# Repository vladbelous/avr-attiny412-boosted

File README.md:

# ATtiny412-based board with on-board boost regulator

Small ATtiny412 board powered by a boost regulator (MCP1640, or pin-compatible MCP16251, TPS6107x; check FB voltage).

Two powering options:
* Li-Ion battery: place voltage-supervisor MIC809 (U2) and R2 pull-down resistor -- this will protect the battery from discharging below 2.93V.
* Single/double AA battery: can skip MIC809 and place R1 instead -- this will put boost regulator in always-on mode.

Optional:
* Power distribution switch IC (MIC9409x) for the common use case of driving a LED strip (WS2812B, APA106, etc), or other, possibly capacitative, loads.
* Pull-up resistors for I2C on botton side (on pins PA1 = SDA, and PA2 = SCL).

Designed with KiCad 5 (www.kicad.org).

## Schematic:

## Layout:

## Assembled:

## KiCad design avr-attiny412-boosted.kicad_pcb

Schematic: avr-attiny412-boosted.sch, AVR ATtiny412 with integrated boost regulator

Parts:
C1: 10uF; 1206_HS
C2: 4.7uF; 1206_HS
C3, C5: 10uF; 1210_HS
C4: 0.1uF; 0805_HS
F1: Polyfuse; 1206_HS
J2, J3, J4, J5, J6, J7, J8, J9, J13, J14, J15: Conn_01x01; Pin_Header_Straight_1x01_Pitch2.54mm
J10, J11, J12: Conn_01x01; Conn_1-wire
JST_PH_BAT1: JST_PH_BAT; JST_PH_S2B-PH-K_02x2.00mm_Angled_WiderHole
L1: 4.7uH; L_Taiyo-Yuden_NR-S-40xx_HS
R1, R2, R6: 100k; 0805_HS
R3, R4: R; 0805_HS
R5: 3.3k; 0805_HS
R7: 1k; 0805_HS
R8, R9: 10k; 0805_HS
SW1: SW_Push; SW_SPST_PUSH_6mm_3mm
U1: MCP1640; SOT-23-6_HS
U2: MIC809; SOT-23_HS
U3: attiny412; SOIC-8_3.9x4.9mm_Pitch1.27mm_HS
U4: MIC9409x; SOT-363_SC-70-6_HS

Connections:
GND: C1.2, C2.2, C3.2, C4.2, C5.2, J5.1, J9.1, J12.1, J15.1, JST_PH_BAT1.2, R2.2, R4.2, R6.2, SW1.2, U1.2, U2.1, U3.8, U4.2, U4.5
unnamed: F1.2, JST_PH_BAT1.1
unnamed: J14.1, R7.1
unnamed: L1.2, U1.1
unnamed: R1.2, R2.1, U1.3, U2.2
unnamed: R3.2, R4.1, U1.4
unnamed: R5.2, SW1.1, U3.6
PA1: J2.1, R8.2, U3.4
PA2: J3.1, R9.2, U3.5
PA3: J4.1, U3.7
PA6: J7.1, R6.1, U3.2, U4.6
PA7: J8.1, R7.2, U3.3
UPDI: J11.1, R5.1
VBAT: C1.1, F1.1, L1.1, R1.1, U1.6, U2.3
VPP: C2.1, C3.1, C4.1, J6.1, J10.1, R3.1, R8.1, R9.1, U1.5, U3.1, U4.4
VSW: C5.1, J13.1, U4.1

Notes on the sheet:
Place either: R2 + MIC809: voltage supervisor enabled (useful when using Li-Ion batteries) or R1: bypass superviser, boost always on (useful when using non-rechargeable)
DNP
Vth = 2.93V
750mA
Pin-compatible with: MCP1640: FB = 1.21V MCP16251: FB = 1.23V TPS61070 / TPS61073: FB = 0.5V
SW1: reset in software or other functionality
optional I2C pull-ups
3 smaller PTHs for programming
Load switch, controlled with PA6
LED strip with data on PA7
push-pull

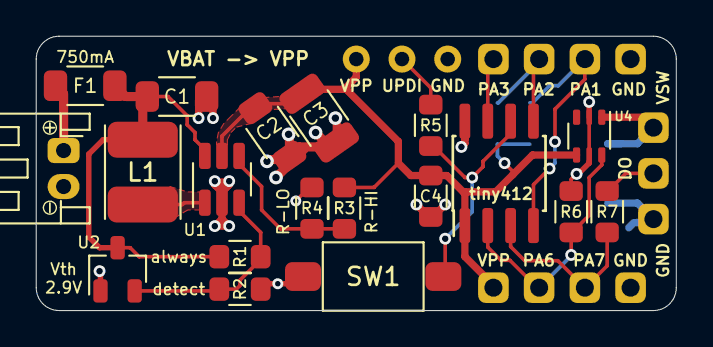
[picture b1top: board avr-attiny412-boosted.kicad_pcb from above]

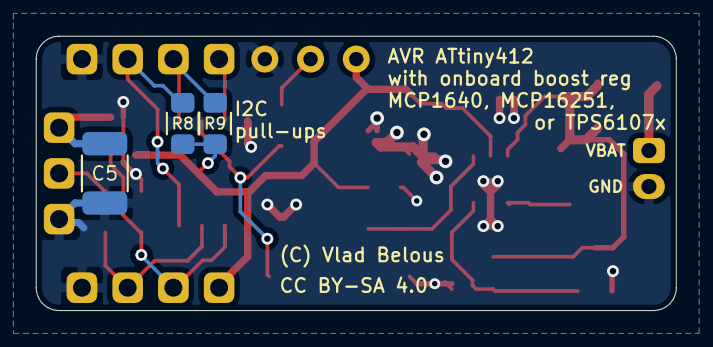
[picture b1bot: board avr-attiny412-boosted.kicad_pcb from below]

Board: 2 copper layers, 35.6 x 15.2 mm, 36 parts (3 on the bottom side), 16 nets.

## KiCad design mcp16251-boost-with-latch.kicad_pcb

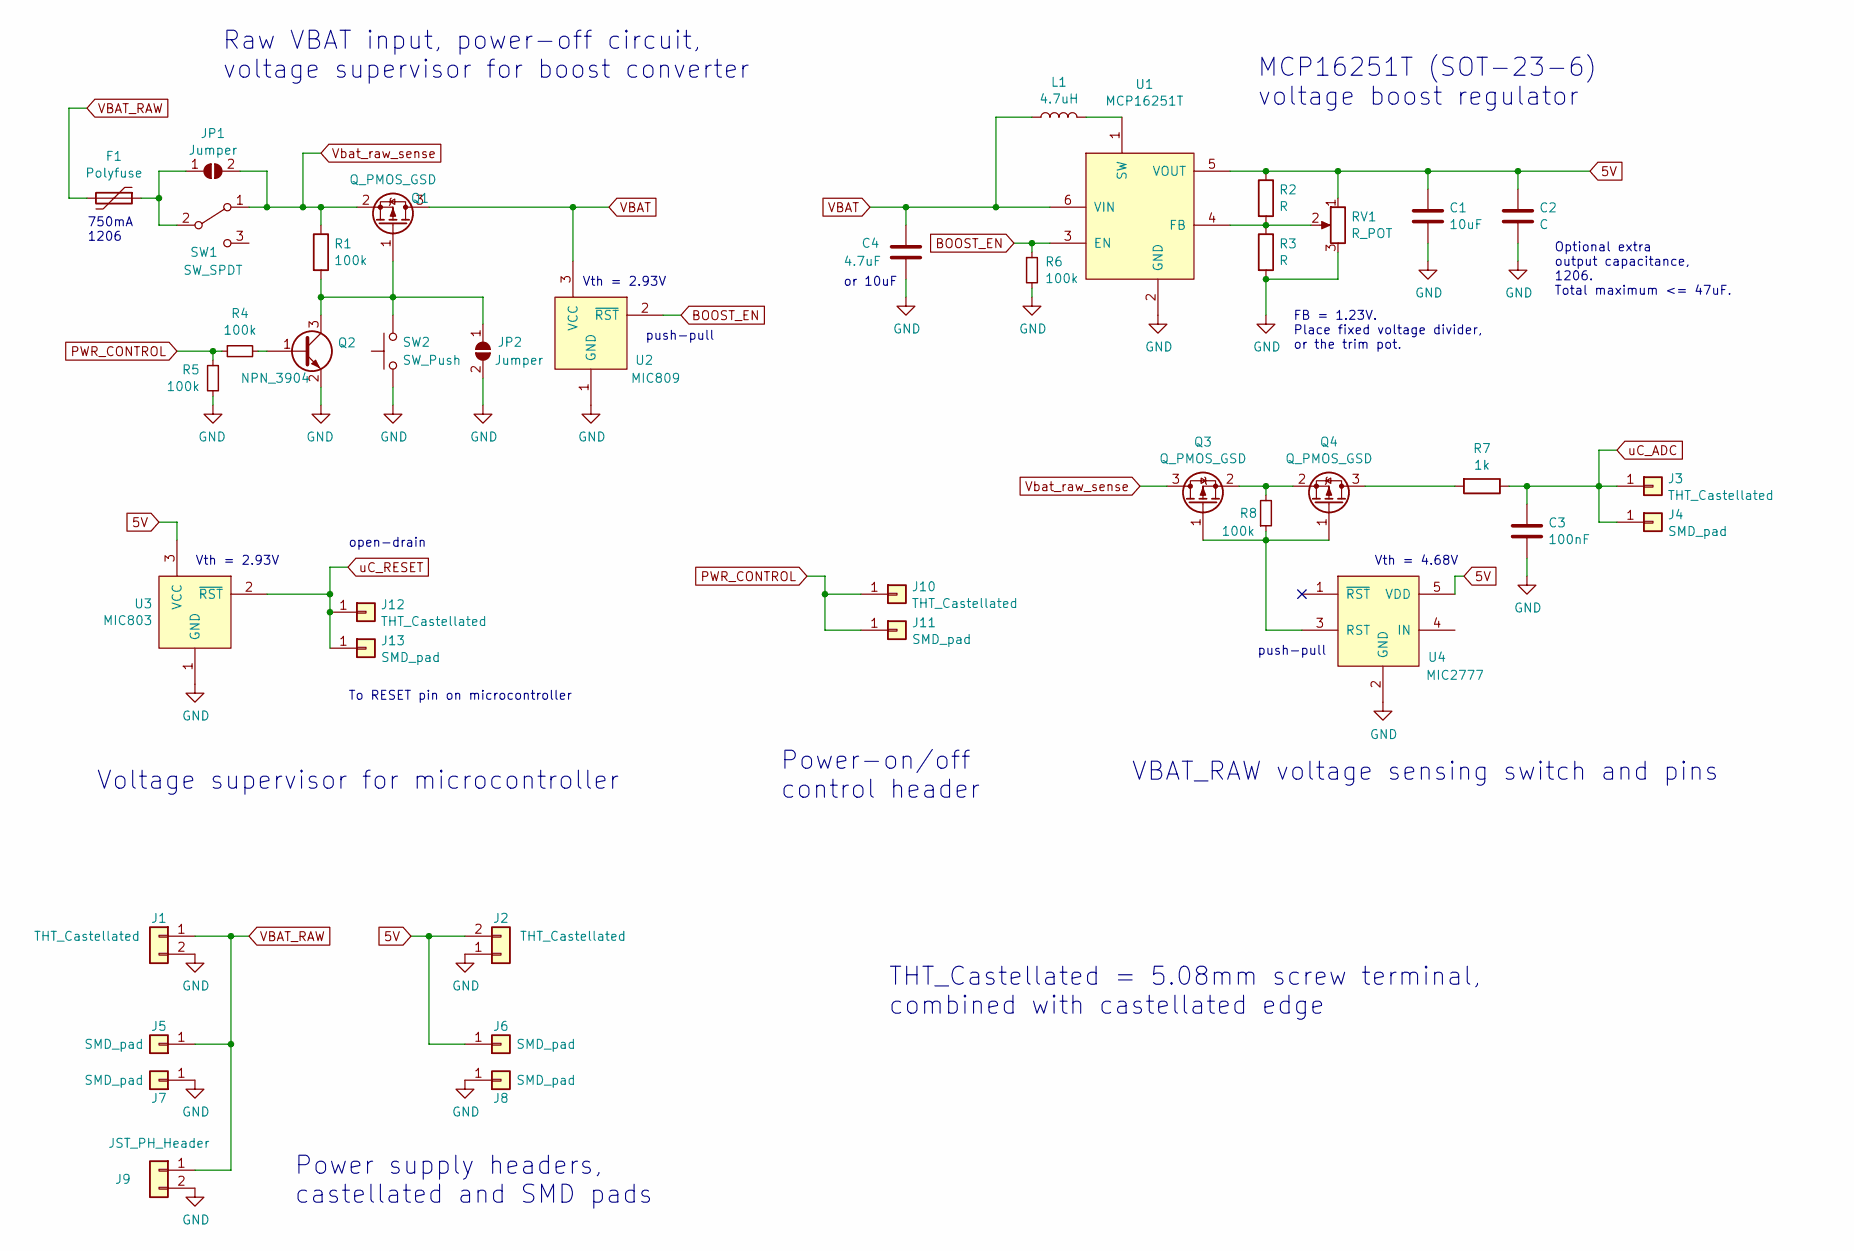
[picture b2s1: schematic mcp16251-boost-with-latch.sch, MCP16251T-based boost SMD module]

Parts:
C1: 10uF; R_1206_HS
C2: C; R_1206_HS
C3: 100nF; R_0805_HS
C4: 4.7uF; R_1206_HS
F1: Polyfuse; R_1206_HS
J1: THT_Castellated; Conn_01x02_cast
J2: THT_Castellated; Conn_01x02_cast_mirrored
J3, J10, J12: THT_Castellated; Conn_01x01_cast
J4, J5, J6, J7, J8, J11, J13: SMD_pad; SMD-Pad_01x01
J9: JST_PH_Header; JST_PH_S2B-PH-K_02x2.00mm_Angled
JP1, JP2: Jumper; R_0805_HS
L1: 4.7uH; L_Taiyo-Yuden_NR-S-40xx_HS
Q1, Q3, Q4: Q_PMOS_GSD; SOT-23_HS
Q2: NPN_3904; SOT-23_HS
R1, R4, R5, R6, R8: 100k; R_0805_HS
R2, R3: R; R_0805_HS
R7: 1k; R_0805_HS
RV1: R_POT; Conn_01x03_small
SW1: SW_SPDT; Conn_01x03_small
SW2: SW_Push; SW_SPST_TL3342
U1: MCP16251T; SOT-23-6_HS
U2: MIC809; SOT-23_HS
U3: MIC803; SOT-23_HS
U4: MIC2777; SOT-23-5_HS

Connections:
5V: C1.1, C2.1, J2.2, J6.1, R2.1, RV1.1, U1.5 (VOUT), U3.3 (VCC), U4.5 (VDD)
BOOST_EN: R6.1, U1.3 (EN), U2.2 (~RST)
GND: C1.2, C2.2, C3.2, C4.2, J1.2, J2.1, J7.1, J8.1, J9.2, JP2.2 (B), Q2.2 (E), R3.2, R5.2, R6.2, RV1.3, SW2.1, U1.2 (GND), U2.1 (GND), U3.1 (GND), U4.2 (GND)
unnamed: F1.1, JP1.1 (A), SW1.2 (B)
unnamed: JP2.1 (A), Q1.1 (G), Q2.3 (C), R1.2, SW2.2
unnamed: L1.2, U1.1 (SW)
unnamed: Q2.1 (B), R4.2
unnamed: Q3.1 (G), Q4.1 (G), R8.1, U4.3 (RST)
unnamed: Q3.2 (S), Q4.2 (S), R8.2
unnamed: Q4.3 (D), R7.2
unnamed: R2.2, R3.1, RV1.2, U1.4 (FB)
PWR_CONTROL: J10.1, J11.1, R4.1, R5.1
VBAT: C4.1, L1.1, Q1.3 (D), U1.6 (VIN), U2.3 (VCC)
VBAT_RAW: F1.2, J1.1, J5.1, J9.1
Vbat_raw_sense: JP1.2 (B), Q1.2 (S), Q3.3 (D), R1.1, SW1.1 (A)
uC_ADC: C3.1, J3.1, J4.1, R7.1
uC_RESET: J12.1, J13.1, U3.2 (~RST)

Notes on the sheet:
Raw VBAT input, power-off circuit, voltage supervisor for boost converter
FB = 1.23V. Place fixed voltage divider, or the trim pot.
MCP16251T (SOT-23-6) voltage boost regulator
or 10uF
Optional extra output capacitance, 1206. Total maximum <= 47uF.
THT_Castellated = 5.08mm screw terminal, combined with castellated edge
Vth = 2.93V
750mA 1206
open-drain
Power supply headers, castellated and SMD pads
Power-on/off control header
Voltage supervisor for microcontroller
To RESET pin on microcontroller
push-pull
Vth = 4.68V
VBAT_RAW voltage sensing switch and pins

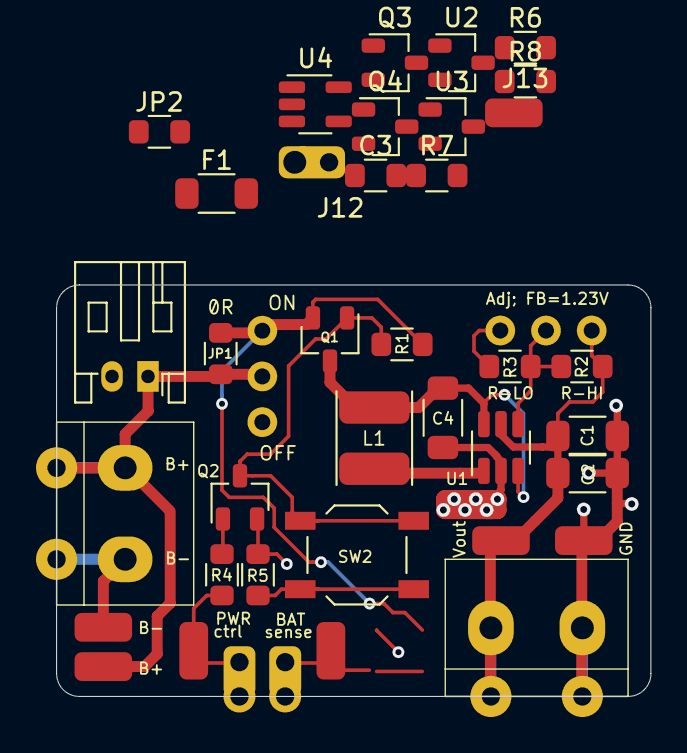
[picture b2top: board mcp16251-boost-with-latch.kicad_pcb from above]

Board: 2 copper layers, 33.0 x 22.9 mm, 40 parts (0 on the bottom side), 17 nets.

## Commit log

2018-12-03 Initial commit. Schematic for MCP16251T-based boost module.
2018-12-03 Added license.
2018-12-03 Battery input SPDT switch
2018-12-03 Create and assign footprints.
2018-12-03 Bugfixes
2018-12-03 Approx layout.
2018-12-03 Set design rules
2018-12-03 MCP16251 layout according to datasheet recommendation
2018-12-03 Further layout
2018-12-03 Try alternative (more square-ish) layout
2018-12-03 Completed alternative layout. Size 1.3in x 0.9in
2018-12-05 Silkscreen texts
2018-12-05 Adjustments
2018-12-08 Fix to relative paths
2018-12-08 Add license
2018-12-08 Add images
2018-12-08 Add README
2018-12-08 Add size info.
2018-12-29 Include voltage supervisors for reliable start and battery protection
2018-12-29 VBAT sense switch using Back-to-back P-MOSFET enabled by MIC2777
2018-12-29 Clean up schematic
2018-12-29 Schematic tuning, footprint assignment, netlist.
2019-04-04 Re-use project
2019-04-04 Partial schematic
2019-04-07 Add load switch symbol, and complete schematic (pending validation)
2019-04-07 Fix LED load capacitor
2019-04-07 Improve footprints (inductor, JST PH, SC-70-6), add JST BAT schematic symbol
2019-04-07 Footprints, minor fixes, footprint assignment, netlist
2019-04-07 Initial PCB arrangement
2019-04-07 Schematic picture
2019-04-07 Approximate placement, no routing
2019-04-08 Routed
2019-04-08 Final layout and silkcreen. Add layout picture
2019-04-08 Adjust prog pin locations
2019-04-22 Clearance update
2019-04-22 Assebled image
2019-04-22 Fix image
2021-11-10 Update README.md
    https://forum.kicad.info/t/warning-avoid-all-links-to-kicad-pcb-org-use-kicad-org/31521

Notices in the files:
avr-attiny412-boosted.kicad_pcb:
CC BY-SA 4.0
avr-attiny412-boosted.sch:
creativecommons.org/licenses
mcp16251-boost-with-latch.kicad_pcb:
CC BY-SA license
(c) Vlad Belous; CC BY-SA
mcp16251-boost-with-latch.sch:
CC BY-SA 4.0 license
